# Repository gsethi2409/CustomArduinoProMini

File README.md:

# CustomArduinoProMini
PCB Design Using KiCAD

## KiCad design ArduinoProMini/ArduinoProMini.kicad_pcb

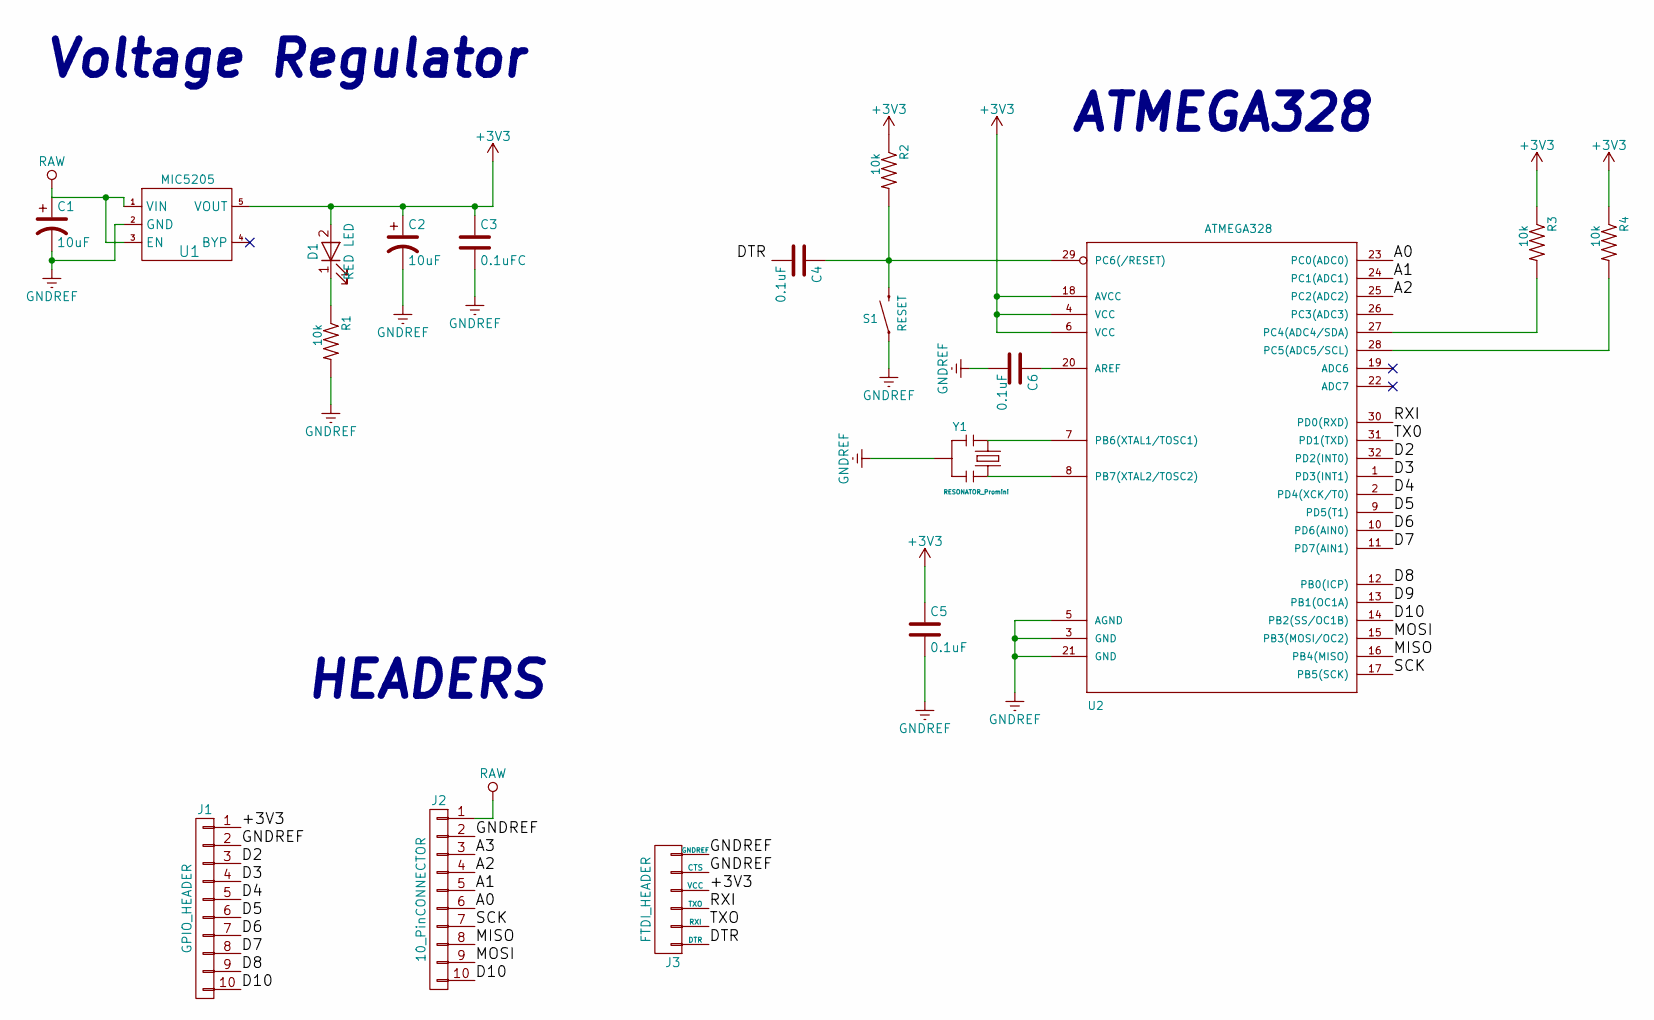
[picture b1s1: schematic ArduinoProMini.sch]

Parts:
C1, C2: 10uF; Polarized Capacitor
C3: 0.1uFC; Capacitor_0603
C4, C5, C6: 0.1uF; Capacitor_0603
D1: RED LED; LED_0603
J1: GPIO_HEADER; Pin_Header_1X10
J2: 10_PinCONNECTOR; Pin_Header_1X10
J3: FTDI_HEADER; Pin_Header_1X06
R1, R2, R3, R4: 10k; Resistor_0603
S1: RESET; RESET SWITCH
U1: MIC5205
U2: ATMEGA328; ATMEGA328_TQFP32-08
Y1: RESONATOR_Promini; RESONATOR-SMD

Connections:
+3V3: C2.1, C3.1, C5.1, D1.2 (A), J1.1, J3.4 (VCC), R2.1, R3.1, R4.1, U1.5 (VOUT), U2.4 (VCC), U2.6 (VCC), U2.18 (AVCC)
/A0: J2.6, U2.23 (PC0(ADC0))
/A1: J2.5, U2.24 (PC1(ADC1))
/A2: J2.4, U2.25 (PC2(ADC2))
/A3: J2.3
/D2: J1.3, U2.32 (PD2(INT0))
/D3: J1.4, U2.1 (PD3(INT1))
/D4: J1.5, U2.2 (PD4(XCK/T0))
/D5: J1.6, U2.9 (PD5(T1))
/D6: J1.7, U2.10 (PD6(AIN0))
/D7: J1.8, U2.11 (PD7(AIN1))
/D8: J1.9, U2.12 (PB0(ICP))
/D9: U2.13 (PB1(OC1A))
/D10: J1.10, J2.10, U2.14 (PB2(SS/OC1B))
/DTR: J3.1 (DTR)
/MISO: J2.8, U2.16 (PB4(MISO))
/MOSI: J2.9, U2.15 (PB3(MOSI/OC2))
/RXI: J3.3 (TXO), U2.30 (PD0(RXD))
/SCK: J2.7, U2.17 (PB5(SCK))
/TX0: U2.31 (PD1(TXD))
/TXO: J3.2 (RXI)
GNDREF: C1.2, C2.2, C3.2, C5.2, C6.2, J1.2, J2.2, J3.5 (CTS), J3.6 (GNDREF), R1.2, S1.1, U1.2 (GND), U2.3 (GND), U2.5 (AGND), U2.21 (GND), Y1.2
unnamed: C4.1, R2.2, S1.2, U2.29 (PC6(/RESET))
unnamed: C6.1, U2.20 (AREF)
unnamed: D1.1 (K), R1.1
unnamed: R3.2, U2.27 (PC4(ADC4/SDA))
unnamed: R4.2, U2.28 (PC5(ADC5/SCL))
unnamed: U2.7 (PB6(XTAL1/TOSC1)), Y1.1
unnamed: U2.8 (PB7(XTAL2/TOSC2)), Y1.3
RAW: C1.1, J2.1, U1.1 (VIN), U1.3 (EN)

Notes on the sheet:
ATMEGA328
HEADERS
Voltage Regulator

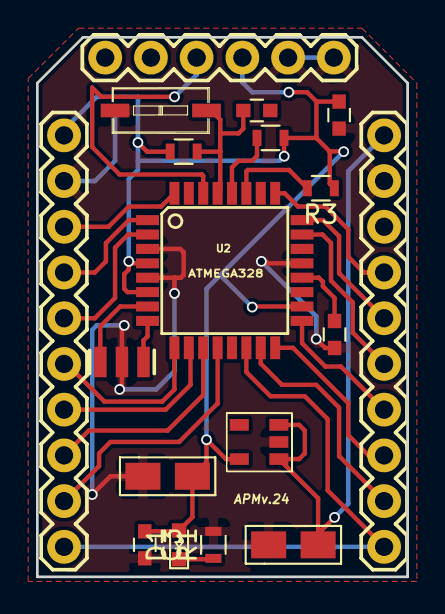
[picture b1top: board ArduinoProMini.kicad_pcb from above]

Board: 2 copper layers, 20.6 x 30.0 mm, 18 parts (0 on the bottom side), 25 nets.

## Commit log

2017-06-21 Add folder: ArduinoProMini
2017-06-21 Add Images
    Front and back views
2017-06-22 Add Folder: ArduinoProMiniLib
    Pre-requisite Files
